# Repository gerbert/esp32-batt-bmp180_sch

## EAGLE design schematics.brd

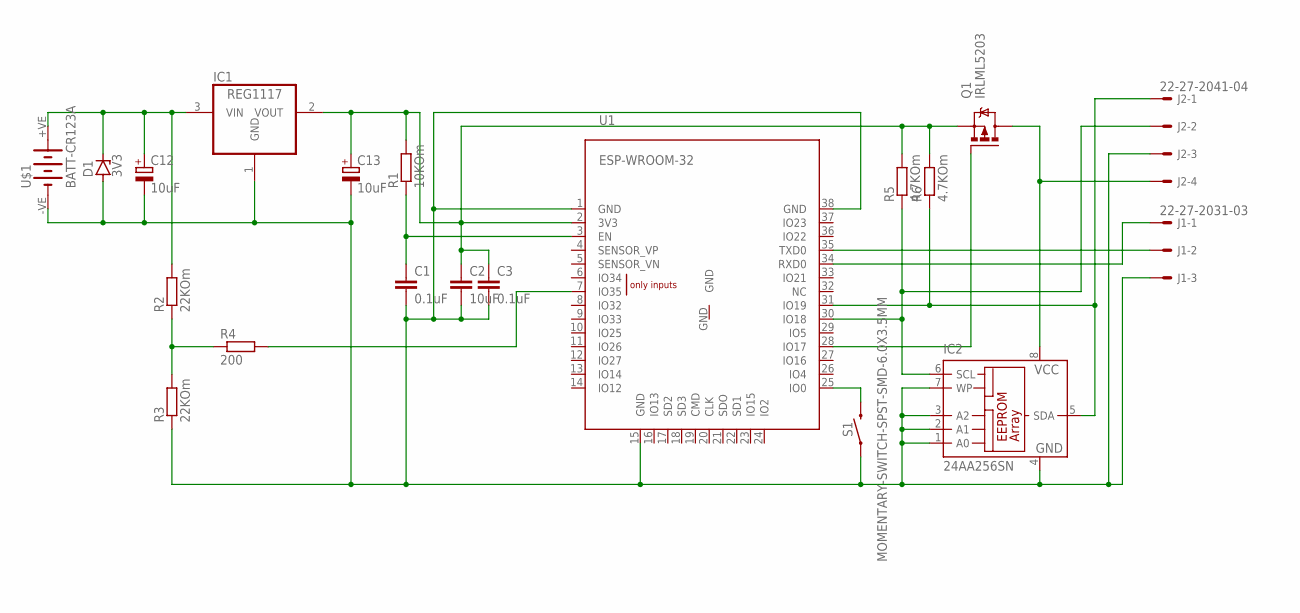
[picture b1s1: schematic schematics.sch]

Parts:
C1, C3: 0.1uF; C1206K
C2: 10uF; C1206K
C12, C13: 10uF; SMC_E
D1: 3V3; SOT223
IC1: REG1117; SOT223
IC2: 24AA256SN; SO-08
J1: 22-27-2031-03; 6410-03
J2: 22-27-2041-04; 6410-04
Q1: IRLML5203; MICRO3
R1: 10KOm; R1206
R2, R3: 22KOm; R1206
R4: 200; R1206
R5, R6: 4.7KOm; R1206
S1: MOMENTARY-SWITCH-SPST-SMD-6.0X3.5MM; TACTILE_SWITCH_SMD_6.0X3.5MM
U1: ESP-WROOM-32
U$1: BATT-CR123A; KEYSTONE-2/3A

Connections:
unnamed: C12.+, D1.4 (C), IC1.3 (VIN), R2.2, U$1.+VE (+)
unnamed: S1.2, U1.25 (IO0)
unnamed: R2.1, R3.2, R4.1
unnamed: C1.2, C2.2, C3.2, C12.-, C13.-, D1.1 (A), IC1.1 (GND), IC2.1 (A0), IC2.2 (A1), IC2.3 (A2), IC2.4 (GND), IC2.7 (WP), J1.3, J2.3, R3.1, S1.1, U1.1 (GND), U1.15 (GND), U1.38 (GND), U$1.-VE (-)
unnamed: C1.1, R1.1, U1.3 (EN)
unnamed: J1.2, U1.35 (TXD0)
unnamed: C2.1, C3.1, C13.+, IC1.2 (VOUT), Q1.2 (S), R1.2, R5.2, R6.2, U1.2 (3V3)
unnamed: R4.2, U1.7 (IO35)
unnamed: J1.1, U1.34 (RXD0)
unnamed: IC2.6 (SCL), J2.2, R5.1, U1.30 (IO18)
unnamed: IC2.5 (SDA), J2.1, R6.1, U1.31 (IO19)
unnamed: Q1.1 (G), U1.28 (IO17)
unnamed: IC2.8 (VCC), J2.4, Q1.3 (D)

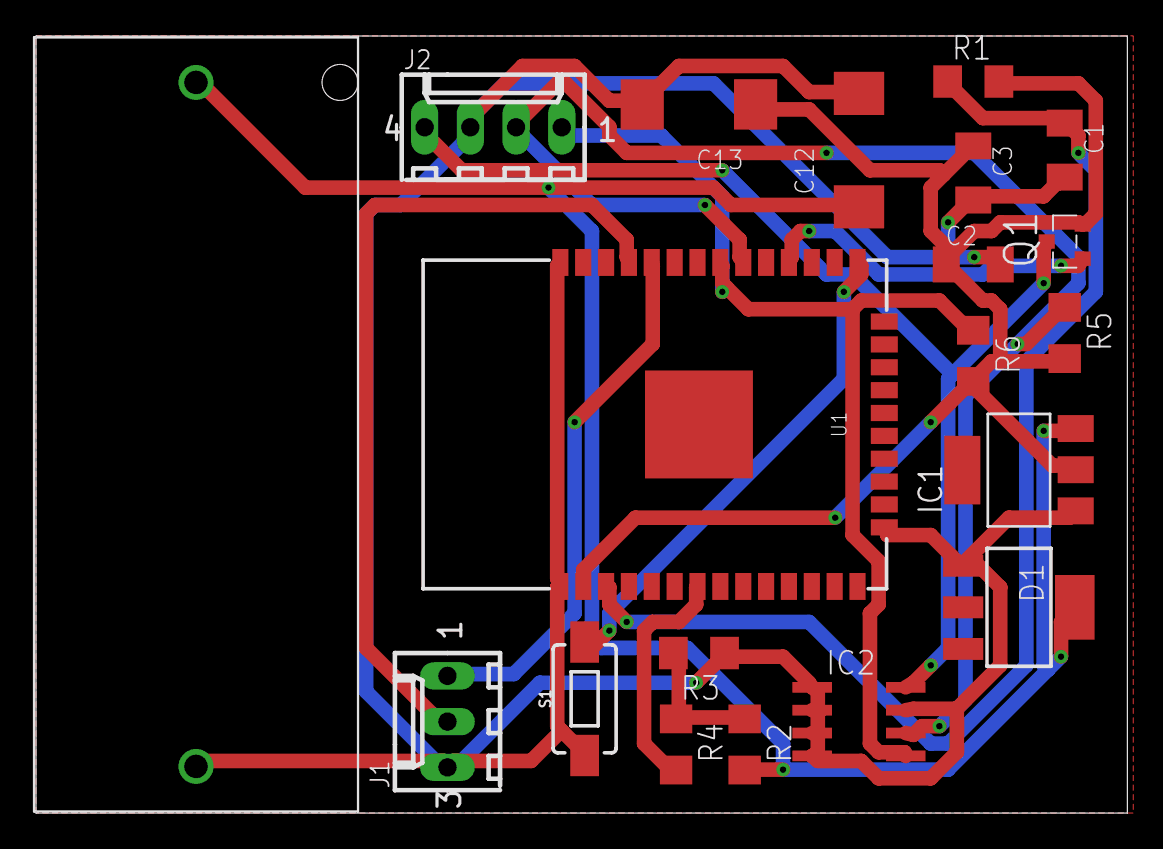
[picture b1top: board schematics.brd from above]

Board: 2 copper layers, 60.6 x 43.2 mm, 20 parts (0 on the bottom side), 13 nets.

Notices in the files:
parts and their libraries:
SparkFun-Switches: Licensing: Creative Commons ShareAlike 4.0 International - https://creativecommons.org/licenses/by-sa/4.0
eagle-library-edeca.net-v5: This is v1 and is licensed under the Creative Commons (Attribution-Non-Commercial-Share Alike 2.0 UK)
